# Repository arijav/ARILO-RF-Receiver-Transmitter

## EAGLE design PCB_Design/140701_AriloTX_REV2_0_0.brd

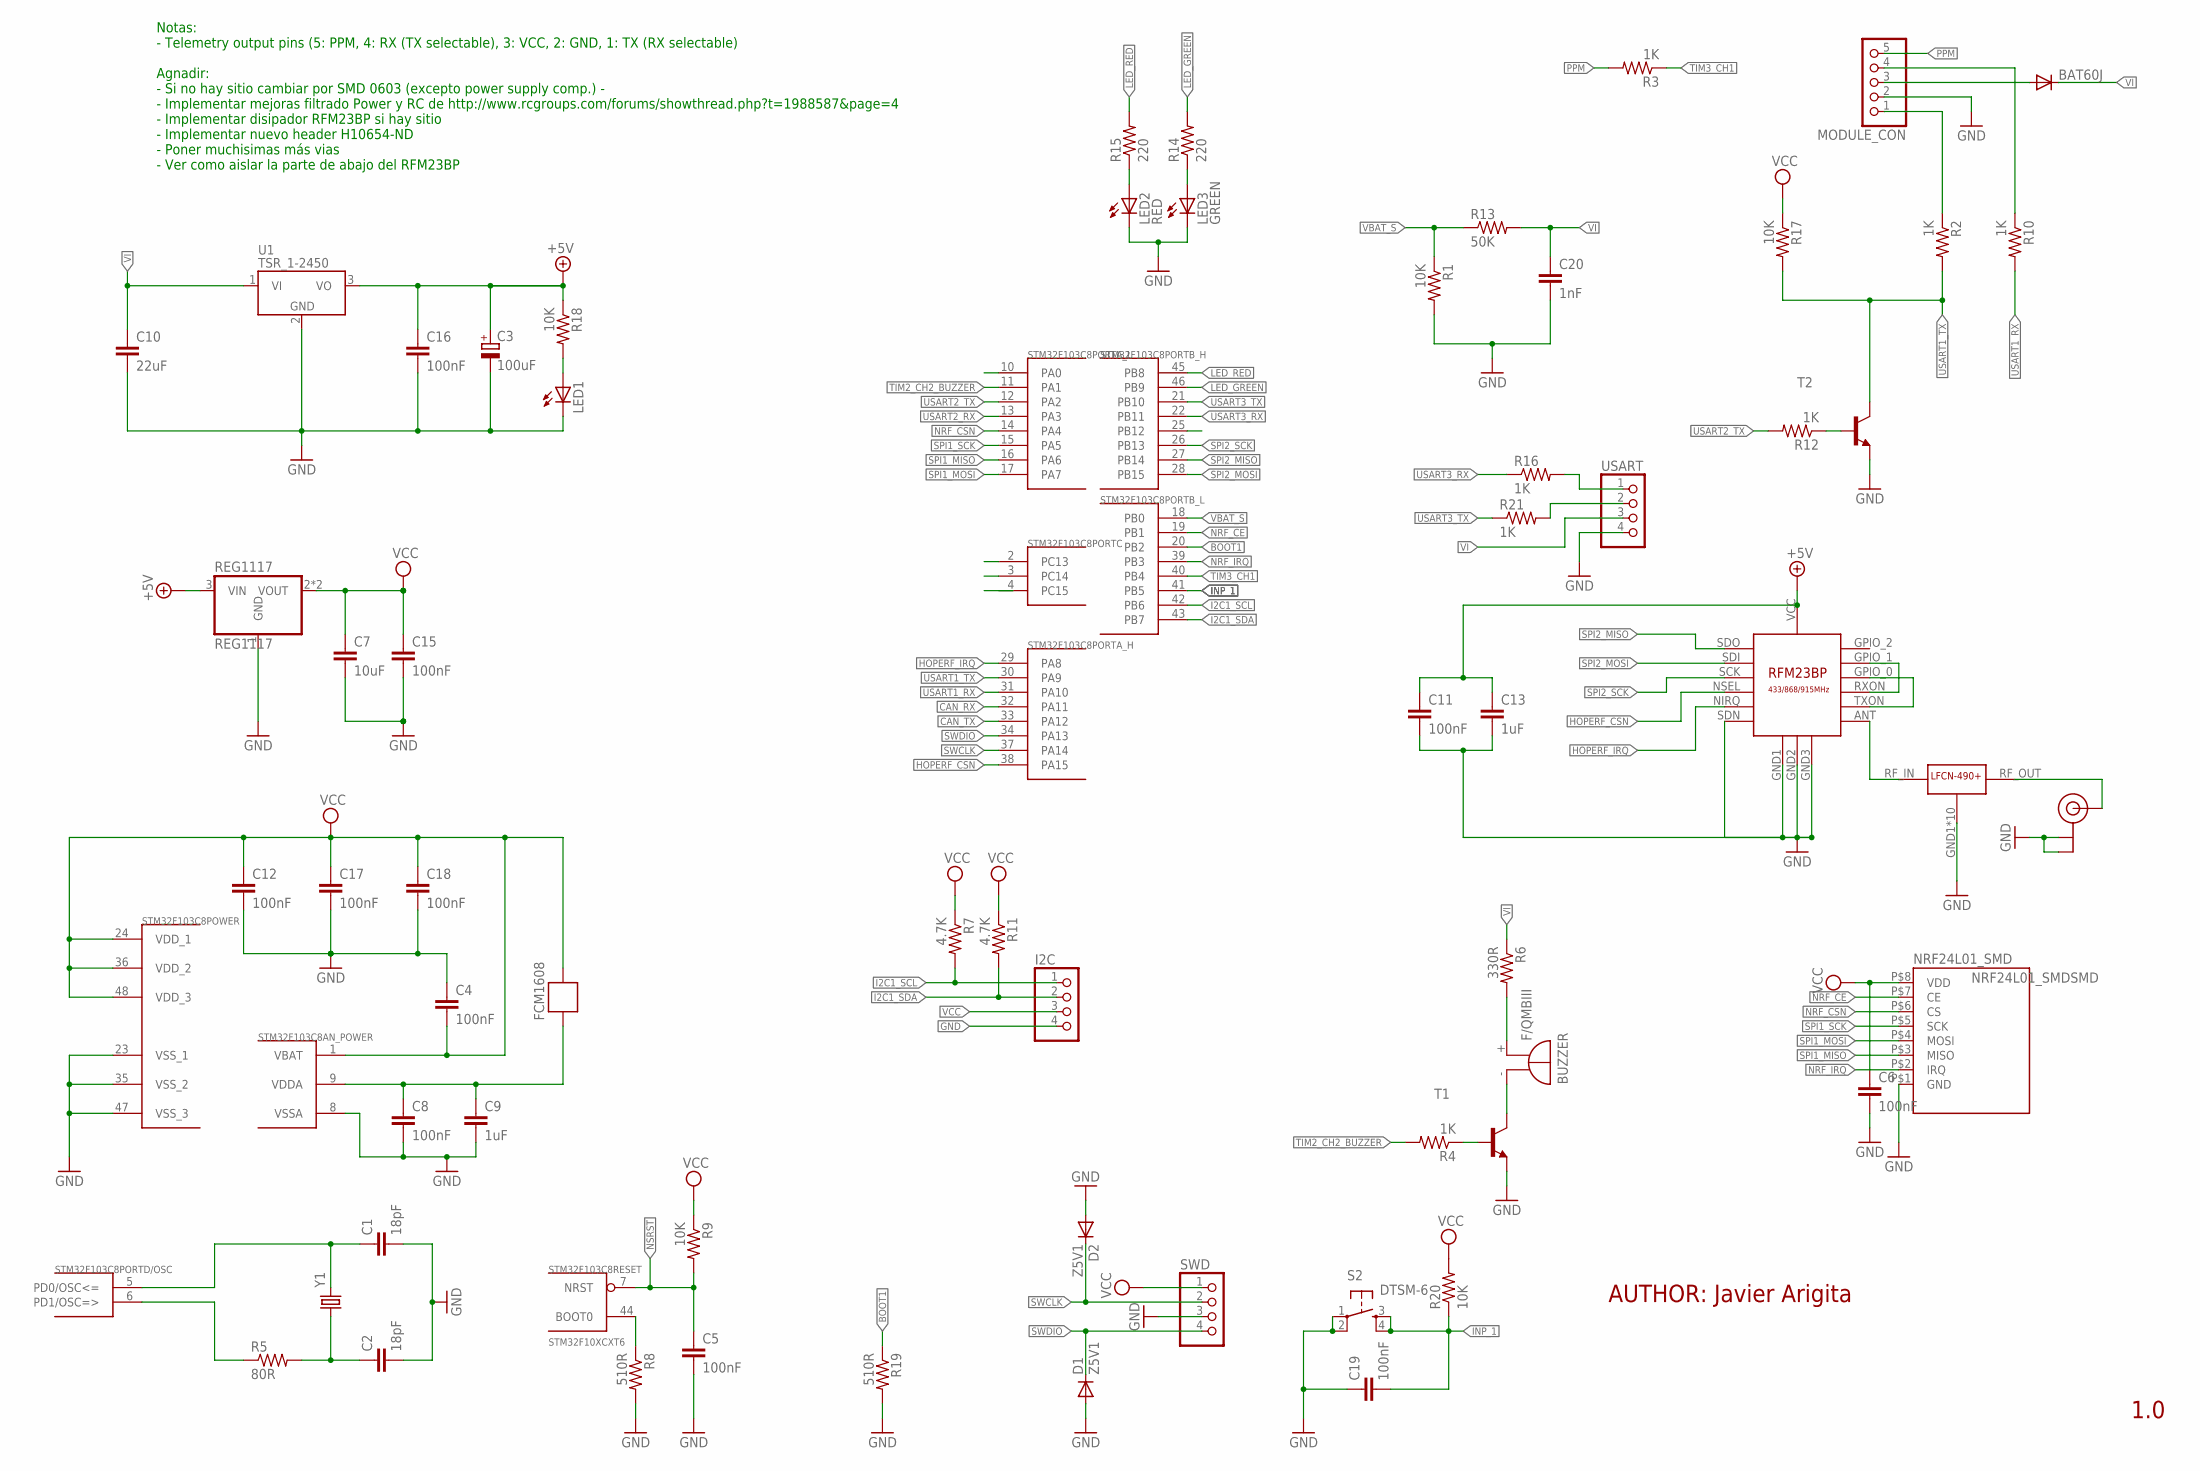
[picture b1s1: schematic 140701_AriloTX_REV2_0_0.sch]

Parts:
BAT60J: DIODE-SOD323-R; SOD323-R
BUZZER: F/QMBIII
C1, C2: 18pF; C0805
C3: 100uF; SMC_B
C4, C5, C6, C8, C11, C12, C15, C16, C17, C18, C19: 100nF; C0805
C7: 10uF; C0805
C9, C13: 1uF; C3216
C10: 22uF; C3216
C20: 1nF; C0805
D1, D2: Z5V1; SOD323-R
FCM1608: FERRITE-BEAD; R0603
I2C: PINHD-1X4; 1X04
LED1: LED0805; CHIPLED_0805
LED2: RED; CHIP-LED0805
LED3: GREEN; CHIP-LED0805
MODULE_CON: PINHD-1X5; 1X05
NRF24L01_SMD: NRF24L01_SMDSMD; NRF24L01_SMD
R1, R9, R17, R18, R20: 10K; R0805
R2, R3, R4, R10, R12, R16, R21: 1K; R0805
R5: 80R; R0805
R6: 330R; R0805
R7, R11: 4.7K; R0805
R8, R19: 510R; R0805
R13: 50K; R0805
R14, R15: 220; R0805
REG1117: REG1117; SOT223
S2: DTSM-6
STM32F103C8: STM32F10XCXT6; TQFP48
SWD: PINHD-1X4; 1X04
T1, T2: BC848-NPN-SOT23-BEC; SOT23-BEC
U1: TSR_1-2450; TSR-1
U$1: RFM23BP
U$2: LFCN490+
U$3: U.FL
USART: PINHD-1X4; 1X04
Y1: CRYSTAL5X3; CRYSTAL-SMD-5X3

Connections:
+5V: C3.+, C11.1, C13.1, C16.1, R18.1, REG1117.3 (VIN), U1.3 (VO), U$1.VCC
BOOT1: R19.1, STM32F103C8.20 (PB2)
CAN_RX: STM32F103C8.32 (PA11)
CAN_TX: STM32F103C8.33 (PA12)
GND: C1.2, C2.2, C3.-, C4.1, C5.2, C6.2, C7.2, C8.2, C9.2, C10.2, C11.2, C12.2, C13.2, C15.2, C16.2, C17.2, C18.2, C19.1, C20.2, D1.A, D2.A, I2C.4, LED1.C, LED2.C, LED3.C, MODULE_CON.2, NRF24L01_SMD.P$1 (GND), R1.2, R8.2, R19.2, REG1117.1 (GND), S2.1, S2.2, STM32F103C8.8 (VSSA), STM32F103C8.23 (VSS_1), STM32F103C8.35 (VSS_2), STM32F103C8.47 (VSS_3), SWD.3, T1.E, T2.E, U1.2 (GND), U$1.GND1, U$1.GND2, U$1.GND3, U$1.SDN, U$2.GND1 (GND), U$2.GND2 (GND), U$2.GND3 (GND), U$2.GND4 (GND), U$2.GND5 (GND), U$2.GND6 (GND), U$2.GND7 (GND), U$2.GND8 (GND), U$2.GND9 (GND), U$2.GND10 (GND), U$3.P$1 (GND), U$3.P$2 (GND), USART.4
HOPERF_CSN: STM32F103C8.38 (PA15), U$1.NSEL
HOPERF_IRQ: STM32F103C8.29 (PA8), U$1.NIRQ
I2C1_SCL: I2C.1, R7.2, STM32F103C8.42 (PB6)
I2C1_SDA: I2C.2, R11.2, STM32F103C8.43 (PB7)
INP_1: C19.2, R20.1, S2.3, S2.4, STM32F103C8.41 (PB5)
LED_GREEN: R14.2, STM32F103C8.46 (PB9)
LED_RED: R15.2, STM32F103C8.45 (PB8)
unnamed: C1.1, STM32F103C8.5 (PD0/OSC<=), Y1.3 (2)
unnamed: R5.1, STM32F103C8.6 (PD1/OSC=>)
unnamed: C2.1, R5.2, Y1.1
unnamed: R8.1, STM32F103C8.44 (BOOT0)
unnamed: R12.1, T2.B
unnamed: MODULE_CON.1, R2.1
unnamed: LED2.A, R15.1
unnamed: LED3.A, R14.1
unnamed: MODULE_CON.4, R10.1
unnamed: LED1.A, R18.2
unnamed: U$1.ANT, U$2.RF_IN (RF_INP)
unnamed: R16.2, USART.1
unnamed: R21.2, USART.2
unnamed: BAT60J.A, MODULE_CON.3
unnamed: BUZZER.+ (-), R6.2
unnamed: C8.1, C9.1, FCM1608.2, STM32F103C8.9 (VDDA)
unnamed: U$2.RF_OUT (RF_OUTP), U$3.P$3 (SIGNAL)
unnamed: R4.1, T1.B
unnamed: BUZZER.- (+), T1.C
unnamed: U$1.GPIO_1, U$1.RXON
unnamed: U$1.GPIO_0, U$1.TXON
NRF_CE: NRF24L01_SMD.P$7 (CE), STM32F103C8.19 (PB1)
NRF_CSN: NRF24L01_SMD.P$6 (CS), STM32F103C8.14 (PA4)
NRF_IRQ: NRF24L01_SMD.P$2 (IRQ), STM32F103C8.39 (PB3)
NSRST: C5.1, R9.2, STM32F103C8.7 (NRST)
PPM: MODULE_CON.5, R3.2
SPI1_MISO: NRF24L01_SMD.P$3 (MISO), STM32F103C8.16 (PA6)
SPI1_MOSI: NRF24L01_SMD.P$4 (MOSI), STM32F103C8.17 (PA7)
SPI1_SCK: NRF24L01_SMD.P$5 (SCK), STM32F103C8.15 (PA5)
SPI2_MISO: STM32F103C8.27 (PB14), U$1.SDO
SPI2_MOSI: STM32F103C8.28 (PB15), U$1.SDI
SPI2_SCK: STM32F103C8.26 (PB13), U$1.SCK
SWCLK: D2.C, STM32F103C8.37 (PA14), SWD.2
SWDIO: D1.C, STM32F103C8.34 (PA13), SWD.4
TIM2_CH2_BUZZER: R4.2, STM32F103C8.11 (PA1)
TIM3_CH1: R3.1, STM32F103C8.40 (PB4)
USART1_RX: R10.2, STM32F103C8.31 (PA10)
USART1_TX: R2.2, R17.2, STM32F103C8.30 (PA9), T2.C
USART2_RX: STM32F103C8.13 (PA3)
USART2_TX: R12.2, STM32F103C8.12 (PA2)
USART3_RX: R16.1, STM32F103C8.22 (PB11)
USART3_TX: R21.1, STM32F103C8.21 (PB10)
VBAT_S: R1.1, R13.1, STM32F103C8.18 (PB0)
VCC: C4.2, C6.1, C7.1, C12.1, C15.1, C17.1, C18.1, FCM1608.1, I2C.3, NRF24L01_SMD.P$8 (VDD), R7.1, R9.1, R11.1, R17.1, R20.2, REG1117.2 (VOUT), REG1117.4 (VOUT), STM32F103C8.1 (VBAT), STM32F103C8.24 (VDD_1), STM32F103C8.36 (VDD_2), STM32F103C8.48 (VDD_3), SWD.1
VI: BAT60J.C, C10.1, C20.1, R6.1, R13.2, U1.1 (VI), USART.3

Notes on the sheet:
AUTHOR: Javier Arigita
1.0
Notas: - Telemetry output pins (5: PPM, 4: RX (TX selectable), 3: VCC, 2: GND, 1: TX (RX selectable) Agnadir: - Si no hay sitio cambiar por SMD 0603 (excepto power supply comp.) - - Implementar mejoras filtrado Power y RC de http://www.rcgroups.com/forums/showthread.php?t=1988587&page=4 - Implement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

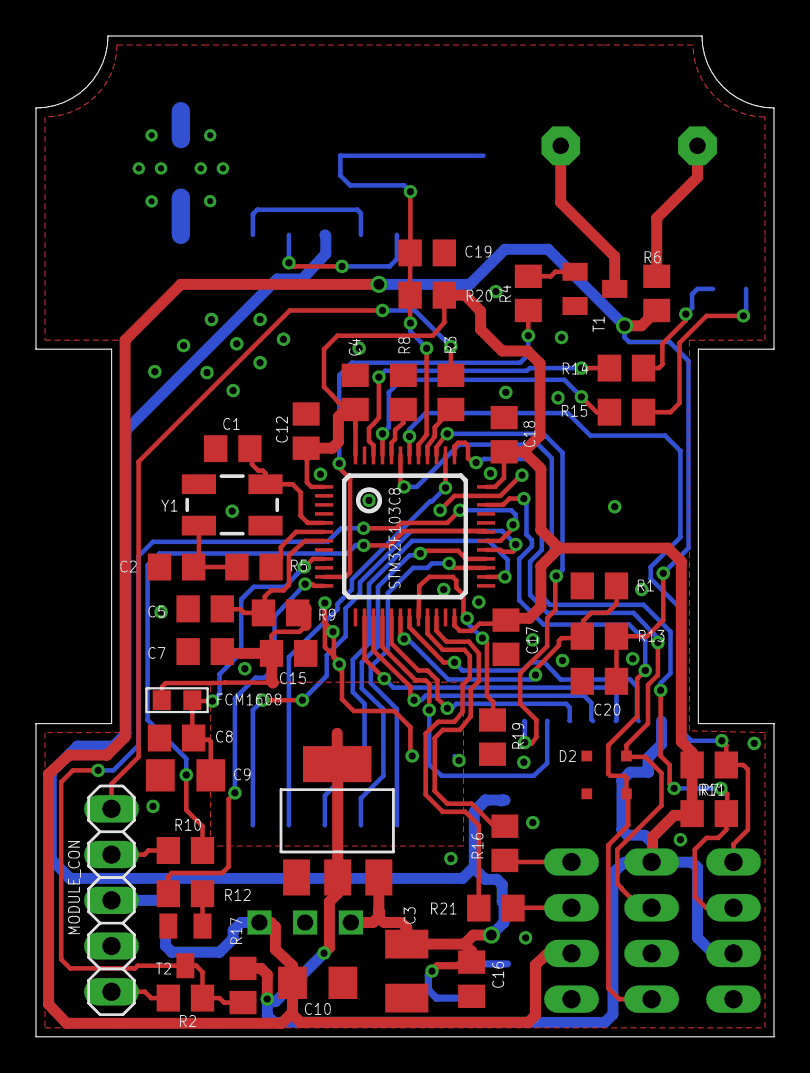
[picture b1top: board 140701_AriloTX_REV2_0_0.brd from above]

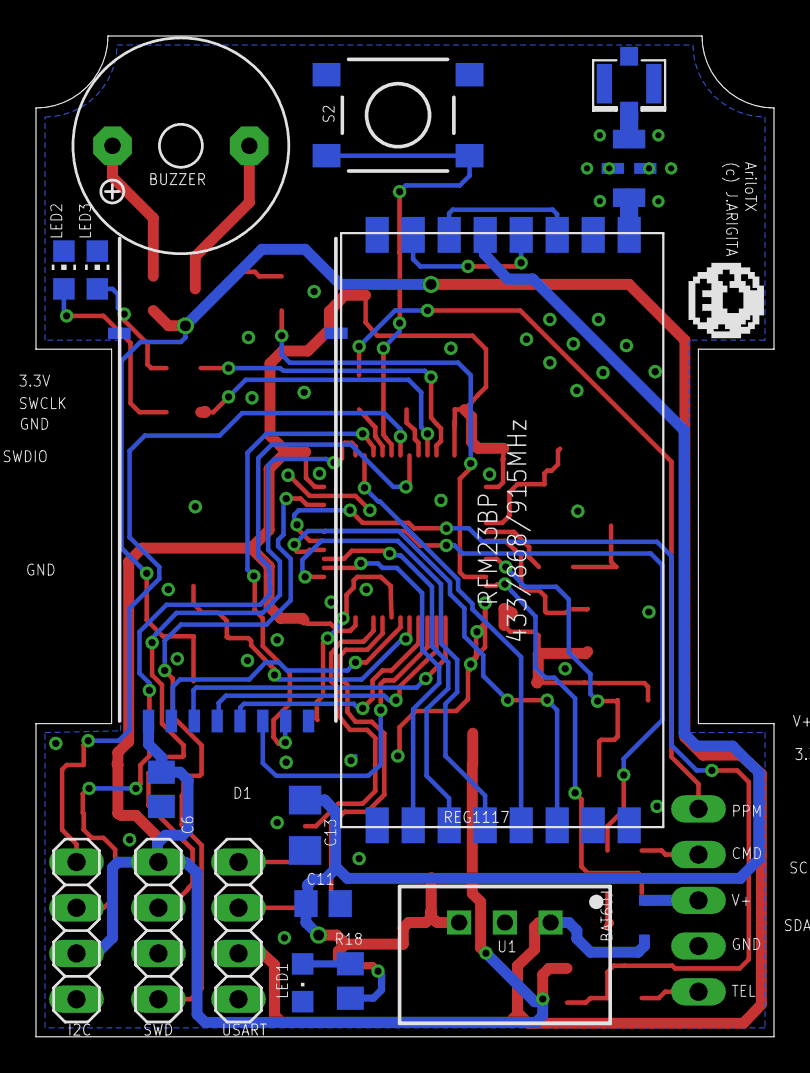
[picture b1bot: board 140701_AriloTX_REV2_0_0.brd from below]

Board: 2 copper layers, 41.0 x 55.6 mm, 63 parts (18 on the bottom side), 54 nets.

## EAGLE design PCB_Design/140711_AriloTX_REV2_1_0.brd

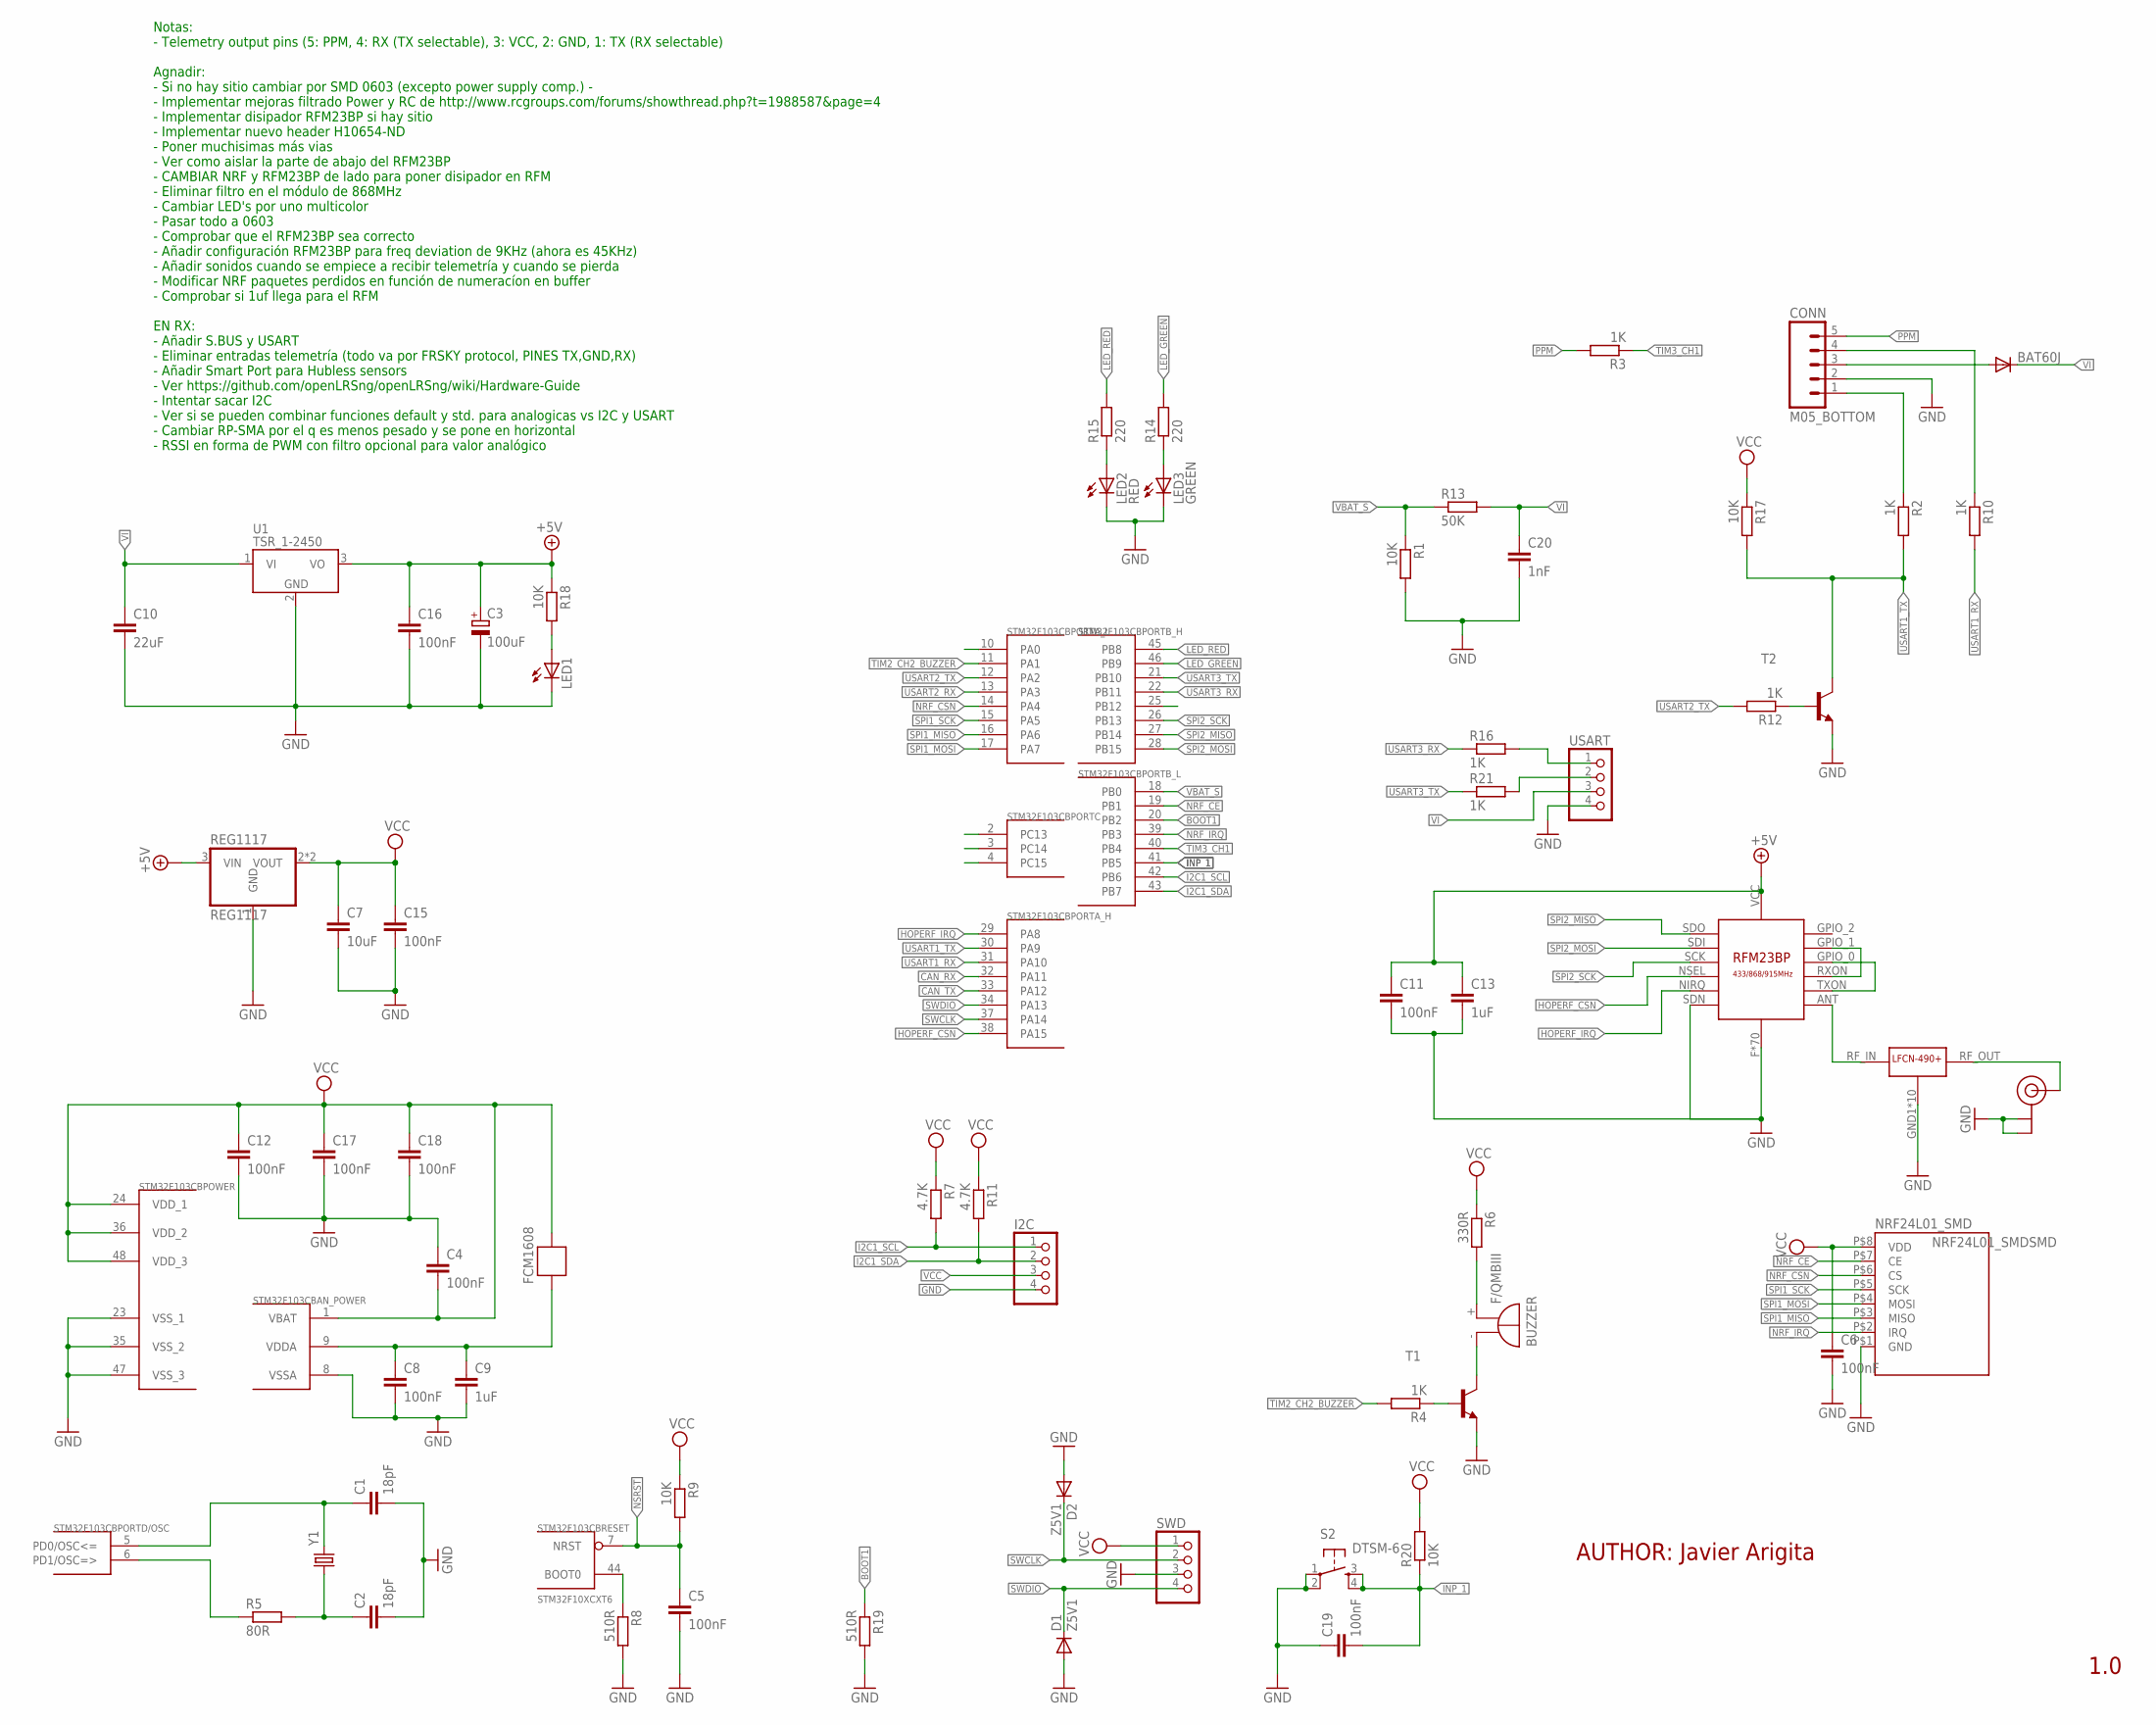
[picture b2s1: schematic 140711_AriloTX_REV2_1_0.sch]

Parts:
BAT60J: DIODE-SOD323-R; SOD323-R
BUZZER: F/QMBIII
C1, C2: 18pF; C0603
C3: 100uF; SMC_B
C4, C5, C6, C8, C11, C12, C15, C16, C17, C18, C19: 100nF; C0603
C7: 10uF; C0805
C9, C13: 1uF; C0603
C10: 22uF; C3216
C20: 1nF; C0603
CONN: M05_BOTTOM
D1, D2: Z5V1; SOD323-R
FCM1608: FERRITE-BEAD; R0603
I2C: PINHD-1X4; 1X04
LED1: LEDCHIP-LED0603; CHIP-LED0603
LED2: RED; CHIP-LED0603
LED3: GREEN; CHIP-LED0603
NRF24L01_SMD: NRF24L01_SMDSMD; NRF24L01_SMD
R1, R9, R17, R18, R20: 10K; R0603
R2, R3, R4, R10, R12, R16, R21: 1K; R0603
R5: 80R; R0603
R6: 330R; R0603
R7, R11: 4.7K; R0603
R8, R19: 510R; R0603
R13: 50K; R0603
R14, R15: 220; R0603
REG1117: REG1117; SOT223
S2: DTSM-6
STM32F103CB: STM32F10XCXT6; TQFP48
SWD: PINHD-1X4; 1X04
T1, T2: BC848-NPN-SOT23-BEC; SOT23-BEC
U1: TSR_1-2450; TSR-1
U$1: RFM23BP
U$2: LFCN490+
U$3: U.FL
USART: PINHD-1X4; 1X04
Y1: CRYSTAL5X3; CRYSTAL-SMD-5X3

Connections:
+5V: C3.+, C11.1, C13.1, C16.1, R18.1, REG1117.3 (VIN), U1.3 (VO), U$1.VCC
BOOT1: R19.1, STM32F103CB.20 (PB2)
CAN_RX: STM32F103CB.32 (PA11)
CAN_TX: STM32F103CB.33 (PA12)
GND: C1.2, C2.2, C3.-, C4.1, C5.2, C6.2, C7.2, C8.2, C9.2, C10.2, C11.2, C12.2, C13.2, C15.2, C16.2, C17.2, C18.2, C19.1, C20.2, CONN.2, D1.A, D2.A, I2C.4, LED1.C, LED2.C, LED3.C, NRF24L01_SMD.P$1 (GND), R1.2, R8.2, R19.2, REG1117.1 (GND), S2.1, S2.2, STM32F103CB.8 (VSSA), STM32F103CB.23 (VSS_1), STM32F103CB.35 (VSS_2), STM32F103CB.47 (VSS_3), SWD.3, T1.E, T2.E, U1.2 (GND), U$1.F (GND), U$1.F1 (GND), U$1.F2 (GND), U$1.F3 (GND), U$1.F4 (GND), U$1.F5 (GND), U$1.F6 (GND), U$1.F7 (GND), U$1.F8 (GND), U$1.F9 (GND), U$1.F10 (GND), U$1.F11 (GND), U$1.F12 (GND), U$1.F13 (GND), U$1.F14 (GND), U$1.F15 (GND), U$1.F16 (GND), U$1.F17 (GND), U$1.F18 (GND), U$1.F19 (GND), U$1.F20 (GND), U$1.F21 (GND), U$1.F22 (GND), U$1.F23 (GND), U$1.F24 (GND), U$1.F25 (GND), U$1.F26 (GND), U$1.F27 (GND), U$1.F28 (GND), U$1.F29 (GND), U$1.F30 (GND), U$1.F31 (GND), U$1.F32 (GND), U$1.F33 (GND), U$1.F34 (GND), U$1.F35 (GND), U$1.F36 (GND), U$1.F37 (GND), U$1.F38 (GND), U$1.F39 (GND), U$1.F40 (GND), U$1.F41 (GND), U$1.F42 (GND), U$1.F43 (GND), U$1.F44 (GND), U$1.F45 (GND), U$1.F46 (GND), U$1.F47 (GND), U$1.F48 (GND), U$1.F49 (GND), U$1.F50 (GND), U$1.F51 (GND), U$1.F52 (GND), U$1.F53 (GND), U$1.F54 (GND), U$1.F55 (GND), U$1.F56 (GND), U$1.F57 (GND), U$1.F58 (GND), U$1.F59 (GND), U$1.F60 (GND), U$1.F61 (GND), U$1.F62 (GND), U$1.F63 (GND), U$1.F64 (GND), U$1.F65 (GND), U$1.GND1 (GND), U$1.GND2 (GND), U$1.GND3 (GND), U$1.GND_HEAT (GND), U$1.SDN, U$2.GND1 (GND), U$2.GND2 (GND), U$2.GND3 (GND), U$2.GND4 (GND), U$2.GND5 (GND), U$2.GND6 (GND), U$2.GND7 (GND), U$2.GND8 (GND), U$2.GND9 (GND), U$2.GND10 (GND), U$3.P$1 (GND), U$3.P$2 (GND), USART.4
HOPERF_CSN: STM32F103CB.38 (PA15), U$1.NSEL
HOPERF_IRQ: STM32F103CB.29 (PA8), U$1.NIRQ
I2C1_SCL: I2C.1, R7.2, STM32F103CB.42 (PB6)
I2C1_SDA: I2C.2, R11.2, STM32F103CB.43 (PB7)
INP_1: C19.2, R20.1, S2.3, S2.4, STM32F103CB.41 (PB5)
LED_GREEN: R14.2, STM32F103CB.46 (PB9)
LED_RED: R15.2, STM32F103CB.45 (PB8)
unnamed: C1.1, STM32F103CB.5 (PD0/OSC<=), Y1.3 (2)
unnamed: R5.1, STM32F103CB.6 (PD1/OSC=>)
unnamed: C2.1, R5.2, Y1.1
unnamed: R8.1, STM32F103CB.44 (BOOT0)
unnamed: R12.1, T2.B
unnamed: CONN.1, R2.1
unnamed: LED2.A, R15.1
unnamed: LED3.A, R14.1
unnamed: CONN.4, R10.1
unnamed: LED1.A, R18.2
unnamed: U$1.ANT, U$2.RF_IN (RF_INP)
unnamed: R16.2, USART.1
unnamed: R21.2, USART.2
unnamed: BAT60J.A, CONN.3
unnamed: BUZZER.+ (-), R6.2
unnamed: C8.1, C9.1, FCM1608.2, STM32F103CB.9 (VDDA)
unnamed: U$2.RF_OUT (RF_OUTP), U$3.P$3 (SIGNAL)
unnamed: R4.1, T1.B
unnamed: BUZZER.- (+), T1.C
unnamed: U$1.GPIO_1, U$1.RXON
unnamed: U$1.GPIO_0, U$1.TXON
NRF_CE: NRF24L01_SMD.P$7 (CE), STM32F103CB.19 (PB1)
NRF_CSN: NRF24L01_SMD.P$6 (CS), STM32F103CB.14 (PA4)
NRF_IRQ: NRF24L01_SMD.P$2 (IRQ), STM32F103CB.39 (PB3)
NSRST: C5.1, R9.2, STM32F103CB.7 (NRST)
PPM: CONN.5, R3.2
SPI1_MISO: NRF24L01_SMD.P$3 (MISO), STM32F103CB.16 (PA6)
SPI1_MOSI: NRF24L01_SMD.P$4 (MOSI), STM32F103CB.17 (PA7)
SPI1_SCK: NRF24L01_SMD.P$5 (SCK), STM32F103CB.15 (PA5)
SPI2_MISO: STM32F103CB.27 (PB14), U$1.SDO
SPI2_MOSI: STM32F103CB.28 (PB15), U$1.SDI
SPI2_SCK: STM32F103CB.26 (PB13), U$1.SCK
SWCLK: D2.C, STM32F103CB.37 (PA14), SWD.2
SWDIO: D1.C, STM32F103CB.34 (PA13), SWD.4
TIM2_CH2_BUZZER: R4.2, STM32F103CB.11 (PA1)
TIM3_CH1: R3.1, STM32F103CB.40 (PB4)
USART1_RX: R10.2, STM32F103CB.31 (PA10)
USART1_TX: R2.2, R17.2, STM32F103CB.30 (PA9), T2.C
USART2_RX: STM32F103CB.13 (PA3)
USART2_TX: R12.2, STM32F103CB.12 (PA2)
USART3_RX: R16.1, STM32F103CB.22 (PB11)
USART3_TX: R21.1, STM32F103CB.21 (PB10)
VBAT_S: R1.1, R13.1, STM32F103CB.18 (PB0)
VCC: C4.2, C6.1, C7.1, C12.1, C15.1, C17.1, C18.1, FCM1608.1, I2C.3, NRF24L01_SMD.P$8 (VDD), R6.1, R7.1, R9.1, R11.1, R17.1, R20.2, REG1117.2 (VOUT), REG1117.4 (VOUT), STM32F103CB.1 (VBAT), STM32F103CB.24 (VDD_1), STM32F103CB.36 (VDD_2), STM32F103CB.48 (VDD_3), SWD.1
VI: BAT60J.C, C10.1, C20.1, R13.2, U1.1 (VI), USART.3

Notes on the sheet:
AUTHOR: Javier Arigita
1.0
Notas: - Telemetry output pins (5: PPM, 4: RX (TX selectable), 3: VCC, 2: GND, 1: TX (RX selectable) Agnadir: - Si no hay sitio cambiar por SMD 0603 (excepto power supply comp.) - - Implementar mejoras filtrado Power y RC de http://www.rcgroups.com/forums/showthread.php?t=1988587&page=4 - Implement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

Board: 2 copper layers, 63 parts (19 on the bottom side), 54 nets, no tracks yet.

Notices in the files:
parts and their libraries:
SparkFun-FreqCtrl: Licensing: CC v3.0 Share-Alike You are welcome to use this library for commercial purposes.
